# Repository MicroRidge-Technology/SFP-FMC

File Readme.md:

# FMC SFP Card

This project is designed to allow using sfp cables with the LVDS pins of an FPGA as opposed to the GTX pins. It provides testpoints to monitor the lvds signals with an oscilliscope.

# Pins Used

| FMC Pin | Logical Name | SFP Channel |
| ------- | ------------ | ----------- |
| D14     | FMC\_LA09\_P | SFP0 rx+    |
| D15     | FMC\_LA09\_N | SFP0 rx-    |
| H7      | FMC\_LA02\_P | SFP0 tx+    |
| H8      | FMC\_LA02\_N | SFP0 tx-    |
| H22     | FMC\_LA19\_P | SFP1 rx+    |
| H23     | FMC\_LA19\_N | SFP1 rx-    |
| H37     | FMC\_LA32\_P | SFP1 tx+    |
| H38     | FMC\_LA32\_N | SFP1 tx-    |

# Schematics
Schmatics are available [here](doc/fmc-sfp.pdf)

# Images

Top

Bottom

# Limitations 

This board is designed to work with low frequency signals (<200MHz)  GHz+ signals will certainly fail.

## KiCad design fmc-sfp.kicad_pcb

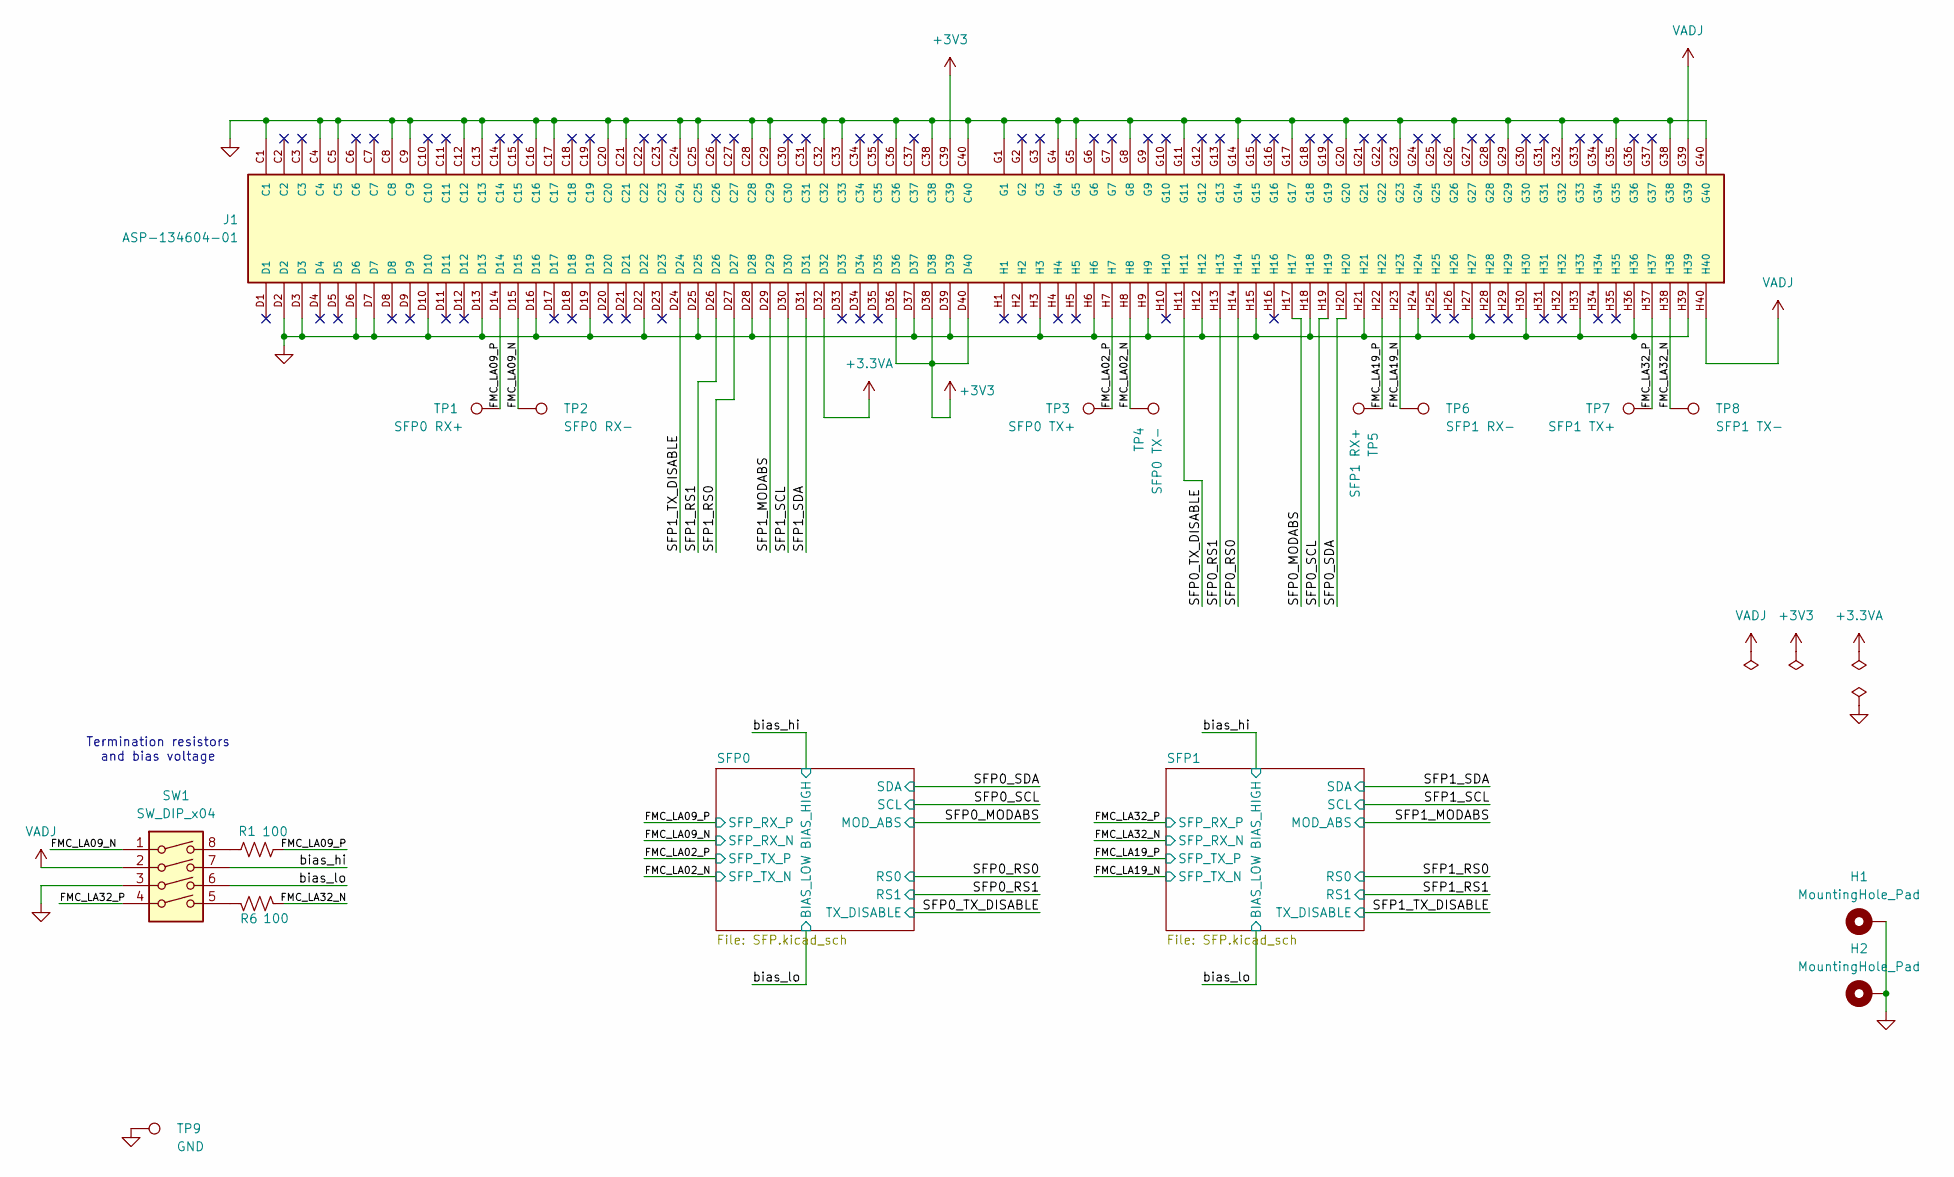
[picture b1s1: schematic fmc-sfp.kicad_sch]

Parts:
H1, H2: MountingHole_Pad; MountingHole_2.7mm_M2.5_ISO14580_Pad
J1: ASP-134604-01; SAMTEC_ASP-134604-01; PARTREV S
R1, R6: 100; R_0805_2012Metric_Pad1.20x1.40mm_HandSolder; MPN 0805W8F1000T5E
SW1: SW_DIP_x04; SW_DIP_SPSTx04_Slide_KingTek_DSHP04TS_W7.62mm_P1.27mm; MPN DSHP04TSGET
TP1: SFP0 RX+; TestPoint_Pad_D2.5mm
TP2: SFP0 RX-; TestPoint_Pad_D2.5mm
TP3: SFP0 TX+; TestPoint_Pad_D2.5mm
TP4: SFP0 TX-; TestPoint_Pad_D2.5mm
TP5: SFP1 RX+; TestPoint_Pad_D2.5mm
TP6: SFP1 RX-; TestPoint_Pad_D2.5mm
TP7: SFP1 TX+; TestPoint_Pad_D2.5mm
TP8: SFP1 TX-; TestPoint_Pad_D2.5mm
TP9: GND; TestPoint_Keystone_5015_Micro-Minature; MPN 5015

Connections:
+3.3VA: J1.D32
+3V3: J1.C39, J1.D36, J1.D38, J1.D40; also elsewhere on the board
/FMC_LA02_N: J1.H8, TP4.1; also elsewhere on the board
/FMC_LA02_P: J1.H7, TP3.1; also elsewhere on the board
/FMC_LA09_N: J1.D15, SW1.1, TP2.1; also elsewhere on the board
/FMC_LA09_P: J1.D14, R1.2, TP1.1; also elsewhere on the board
/FMC_LA19_N: J1.H23, TP6.1; also elsewhere on the board
/FMC_LA19_P: J1.H22, TP5.1; also elsewhere on the board
/FMC_LA32_N: J1.H38, R6.2, TP8.1; also elsewhere on the board
/FMC_LA32_P: J1.H37, SW1.4, TP7.1; also elsewhere on the board
/SFP0_MODABS: J1.H17; also elsewhere on the board
/SFP0_RS0: J1.H14; also elsewhere on the board
/SFP0_RS1: J1.H13; also elsewhere on the board
/SFP0_SCL: J1.H19; also elsewhere on the board
/SFP0_SDA: J1.H20; also elsewhere on the board
/SFP0_TX_DISABLE: J1.H11; also elsewhere on the board
/SFP1_MODABS: J1.D29; also elsewhere on the board
/SFP1_RS0: J1.D27; also elsewhere on the board
/SFP1_RS1: J1.D26; also elsewhere on the board
/SFP1_SCL: J1.D30; also elsewhere on the board
/SFP1_SDA: J1.D31; also elsewhere on the board
/SFP1_TX_DISABLE: J1.D24; also elsewhere on the board
/bias_hi: SW1.7; also elsewhere on the board
/bias_lo: SW1.6; also elsewhere on the board
GND: H1.1, H2.1, J1.C1, J1.C4, J1.C5, J1.C8, J1.C9, J1.C12, J1.C13, J1.C16, J1.C17, J1.C20, J1.C21, J1.C24, J1.C25, J1.C28, J1.C29, J1.C32, J1.C33, J1.C36, J1.C38, J1.C40, J1.D2, J1.D3, J1.D6, J1.D7, J1.D10, J1.D13, J1.D16, J1.D19, J1.D22, J1.D25, J1.D28, J1.D37, J1.D39, J1.G1, J1.G4, J1.G5, J1.G8, J1.G11, J1.G14, J1.G17, J1.G20, J1.G23, J1.G26, J1.G29, J1.G32, J1.G35, J1.G38, J1.G40, J1.H3, J1.H6, J1.H9, J1.H12, J1.H15, J1.H18, J1.H21, J1.H24, J1.H27, J1.H30, J1.H33, J1.H36, J1.H39, SW1.3, TP9.1; also elsewhere on the board
unnamed: R1.1, SW1.8
unnamed: R6.1, SW1.5
VADJ: J1.G39, J1.H40, SW1.2; also elsewhere on the board

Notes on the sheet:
Termination resistors and bias voltage

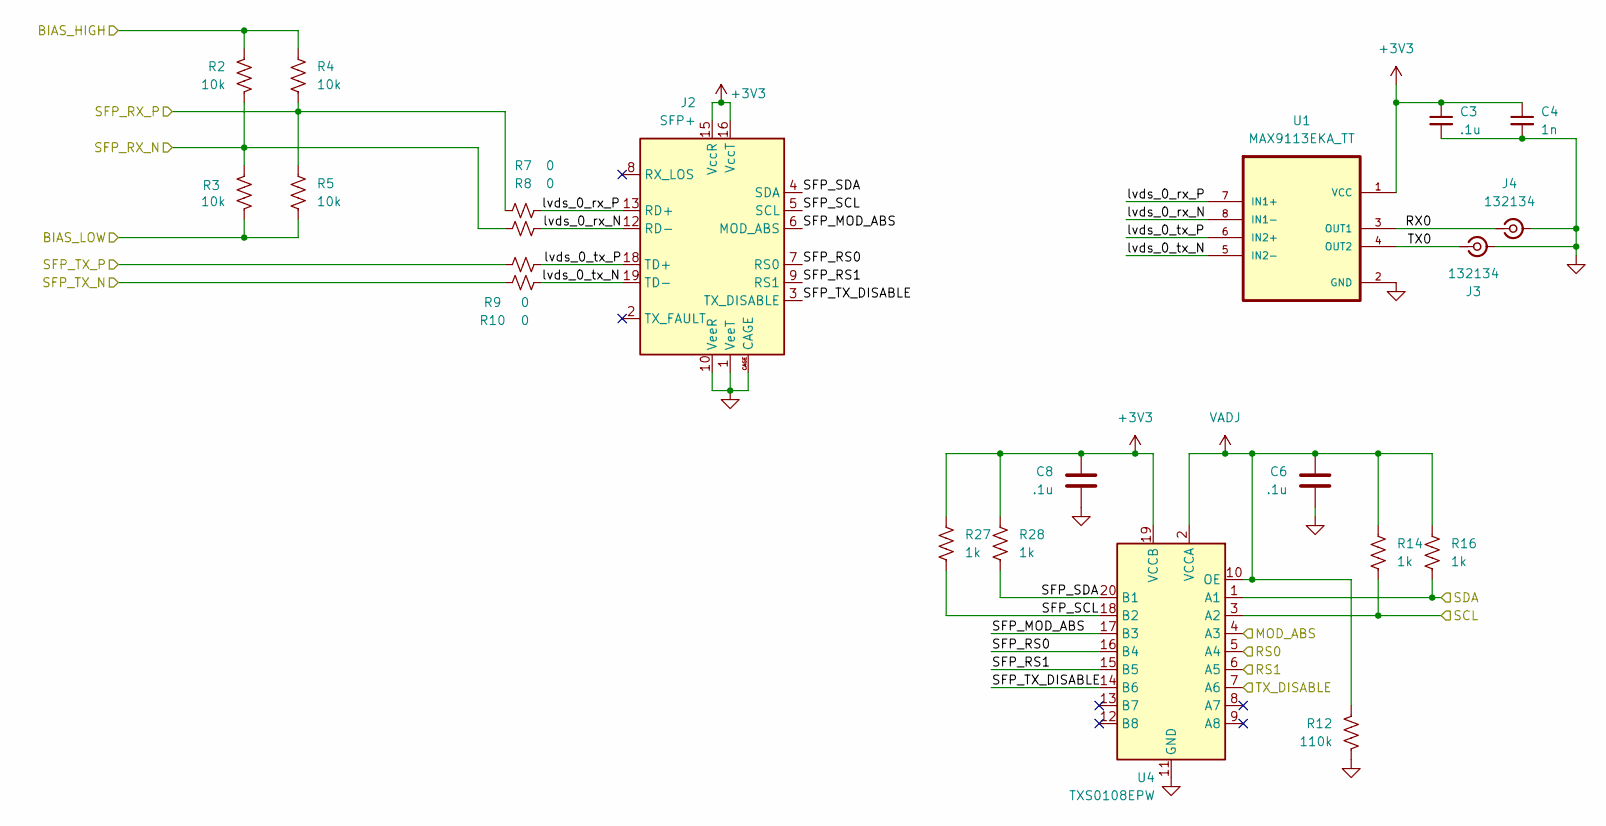
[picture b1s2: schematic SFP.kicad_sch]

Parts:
C3, C6, C8: .1u; C_0603_1608Metric; MPN C0603C104M5RAC7867
C4: 1n; C_0603_1608Metric; MPN C0603C102K5RAC7867
J2: SFP+; SFP_and_Cage; MPN SFPK-SL
J3, J4: 132134; SMA_Amphenol_132134_Vertical; MPN 132134
R2, R3, R4, R5: 10k; R_0805_2012Metric_Pad1.20x1.40mm_HandSolder; MPN 0805W8F1002T5E
R7, R8, R9, R10: 0; R_0805_2012Metric_Pad1.20x1.40mm_HandSolder; MPN 0805W8F0000T5E
R12: 110k; R_0805_2012Metric_Pad1.20x1.40mm_HandSolder; MPN 0805W8F1103T5E
R14, R16, R27, R28: 1k; R_0805_2012Metric_Pad1.20x1.40mm_HandSolder; MPN 0805W8F1001T5E
U1: MAX9113EKA_TT; SOT-23-8; MPN MAX9113EKA+T
U4: TXS0108EPW; TSSOP-20_4.4x6.5mm_P0.65mm; MPN TXS0108EPW

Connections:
+3V3: C3.1, C4.1, C8.1, J2.15 (VccR), J2.16 (VccT), R27.1, R28.1, U1.1 (VCC), U4.19 (VCCB); also elsewhere on the board
/FMC_LA19_N: R10.1; also elsewhere on the board
/FMC_LA19_P: R9.1; also elsewhere on the board
/FMC_LA32_N: R2.2, R3.1, R8.1; also elsewhere on the board
/FMC_LA32_P: R4.2, R5.1, R7.1; also elsewhere on the board
/SFP1/RX0: J4.1 (In), U1.3 (OUT1)
/SFP1/SFP_MOD_ABS: J2.6 (MOD_ABS), U4.17 (B3)
/SFP1/SFP_RS0: J2.7 (RS0), U4.16 (B4)
/SFP1/SFP_RS1: J2.9 (RS1), U4.15 (B5)
/SFP1/SFP_SCL: J2.5 (SCL), R27.2, U4.18 (B2)
/SFP1/SFP_SDA: J2.4 (SDA), R28.2, U4.20 (B1)
/SFP1/SFP_TX_DISABLE: J2.3 (TX_DISABLE), U4.14 (B6)
/SFP1/TX0: J3.1 (In), U1.4 (OUT2)
/SFP1/lvds_0_rx_N: J2.12 (RD-), R8.2, U1.8 (IN1-)
/SFP1/lvds_0_rx_P: J2.13 (RD+), R7.2, U1.7 (IN1+)
/SFP1/lvds_0_tx_N: J2.19 (TD-), R10.2, U1.5 (IN2-)
/SFP1/lvds_0_tx_P: J2.18 (TD+), R9.2, U1.6 (IN2+)
/SFP1_MODABS: U4.4 (A3); also elsewhere on the board
/SFP1_RS0: U4.5 (A4); also elsewhere on the board
/SFP1_RS1: U4.6 (A5); also elsewhere on the board
/SFP1_SCL: R14.2, U4.3 (A2); also elsewhere on the board
/SFP1_SDA: R16.2, U4.1 (A1); also elsewhere on the board
/SFP1_TX_DISABLE: U4.7 (A6); also elsewhere on the board
/bias_hi: R2.1, R4.1; also elsewhere on the board
/bias_lo: R3.2, R5.2; also elsewhere on the board
GND: C3.2, C4.2, C6.2, C8.2, J2.1 (VeeT), J2.10 (VeeR), J2.11 (VeeR), J2.14 (VeeR), J2.17 (VeeT), J2.20 (VeeT), J2.CAGE, J3.2 (Ext), J4.2 (Ext), R12.2, U1.2 (GND), U4.11 (GND); also elsewhere on the board
VADJ: C6.1, R12.1, R14.1, R16.1, U4.2 (VCCA), U4.10 (OE); also elsewhere on the board

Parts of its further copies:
C1, C5, C7: .1u; C_0603_1608Metric; MPN C0603C104M5RAC7867
C2: 1n; C_0603_1608Metric; MPN C0603C102K5RAC7867
J8: SFP+; SFP_and_Cage; MPN SFPK-SL
J9, J10: 132134; SMA_Amphenol_132134_Vertical; MPN 132134
R11: 110k; R_0805_2012Metric_Pad1.20x1.40mm_HandSolder; MPN 0805W8F1103T5E
R13, R15, R17, R18: 1k; R_0805_2012Metric_Pad1.20x1.40mm_HandSolder; MPN 0805W8F1001T5E
R19, R20, R21, R22: 10k; R_0805_2012Metric_Pad1.20x1.40mm_HandSolder; MPN 0805W8F1002T5E
R23, R24, R25, R26: 0; R_0805_2012Metric_Pad1.20x1.40mm_HandSolder; MPN 0805W8F0000T5E
U2: TXS0108EPW; TSSOP-20_4.4x6.5mm_P0.65mm; MPN TXS0108EPW
U3: MAX9113EKA_TT; SOT-23-8; MPN MAX9113EKA+T

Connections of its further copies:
+3V3: C1.1, C2.1, C7.1, J8.15 (VccR), J8.16 (VccT), R17.1, R18.1, U2.19 (VCCB), U3.1 (VCC); also elsewhere on the board
/FMC_LA02_N: R26.1; also elsewhere on the board
/FMC_LA02_P: R25.1; also elsewhere on the board
/FMC_LA09_N: R19.2, R20.1, R24.1; also elsewhere on the board
/FMC_LA09_P: R21.2, R22.1, R23.1; also elsewhere on the board
/SFP0/RX0: J10.1 (In), U3.3 (OUT1)
/SFP0/SFP_MOD_ABS: J8.6 (MOD_ABS), U2.17 (B3)
/SFP0/SFP_RS0: J8.7 (RS0), U2.16 (B4)
/SFP0/SFP_RS1: J8.9 (RS1), U2.15 (B5)
/SFP0/SFP_SCL: J8.5 (SCL), R17.2, U2.18 (B2)
/SFP0/SFP_SDA: J8.4 (SDA), R18.2, U2.20 (B1)
/SFP0/SFP_TX_DISABLE: J8.3 (TX_DISABLE), U2.14 (B6)
/SFP0/TX0: J9.1 (In), U3.4 (OUT2)
/SFP0/lvds_0_rx_N: J8.12 (RD-), R24.2, U3.8 (IN1-)
/SFP0/lvds_0_rx_P: J8.13 (RD+), R23.2, U3.7 (IN1+)
/SFP0/lvds_0_tx_N: J8.19 (TD-), R26.2, U3.5 (IN2-)
/SFP0/lvds_0_tx_P: J8.18 (TD+), R25.2, U3.6 (IN2+)
/SFP0_MODABS: U2.4 (A3); also elsewhere on the board
/SFP0_RS0: U2.5 (A4); also elsewhere on the board
/SFP0_RS1: U2.6 (A5); also elsewhere on the board
/SFP0_SCL: R13.2, U2.3 (A2); also elsewhere on the board
/SFP0_SDA: R15.2, U2.1 (A1); also elsewhere on the board
/SFP0_TX_DISABLE: U2.7 (A6); also elsewhere on the board
/bias_hi: R19.1, R21.1; also elsewhere on the board
/bias_lo: R20.2, R22.2; also elsewhere on the board
GND: C1.2, C2.2, C5.2, C7.2, J8.1 (VeeT), J8.10 (VeeR), J8.11 (VeeR), J8.14 (VeeR), J8.17 (VeeT), J8.20 (VeeT), J8.CAGE, J9.2 (Ext), J10.2 (Ext), R11.2, U2.11 (GND), U3.2 (GND); also elsewhere on the board
VADJ: C5.1, R11.1, R13.1, R15.1, U2.2 (VCCA), U2.10 (OE); also elsewhere on the board

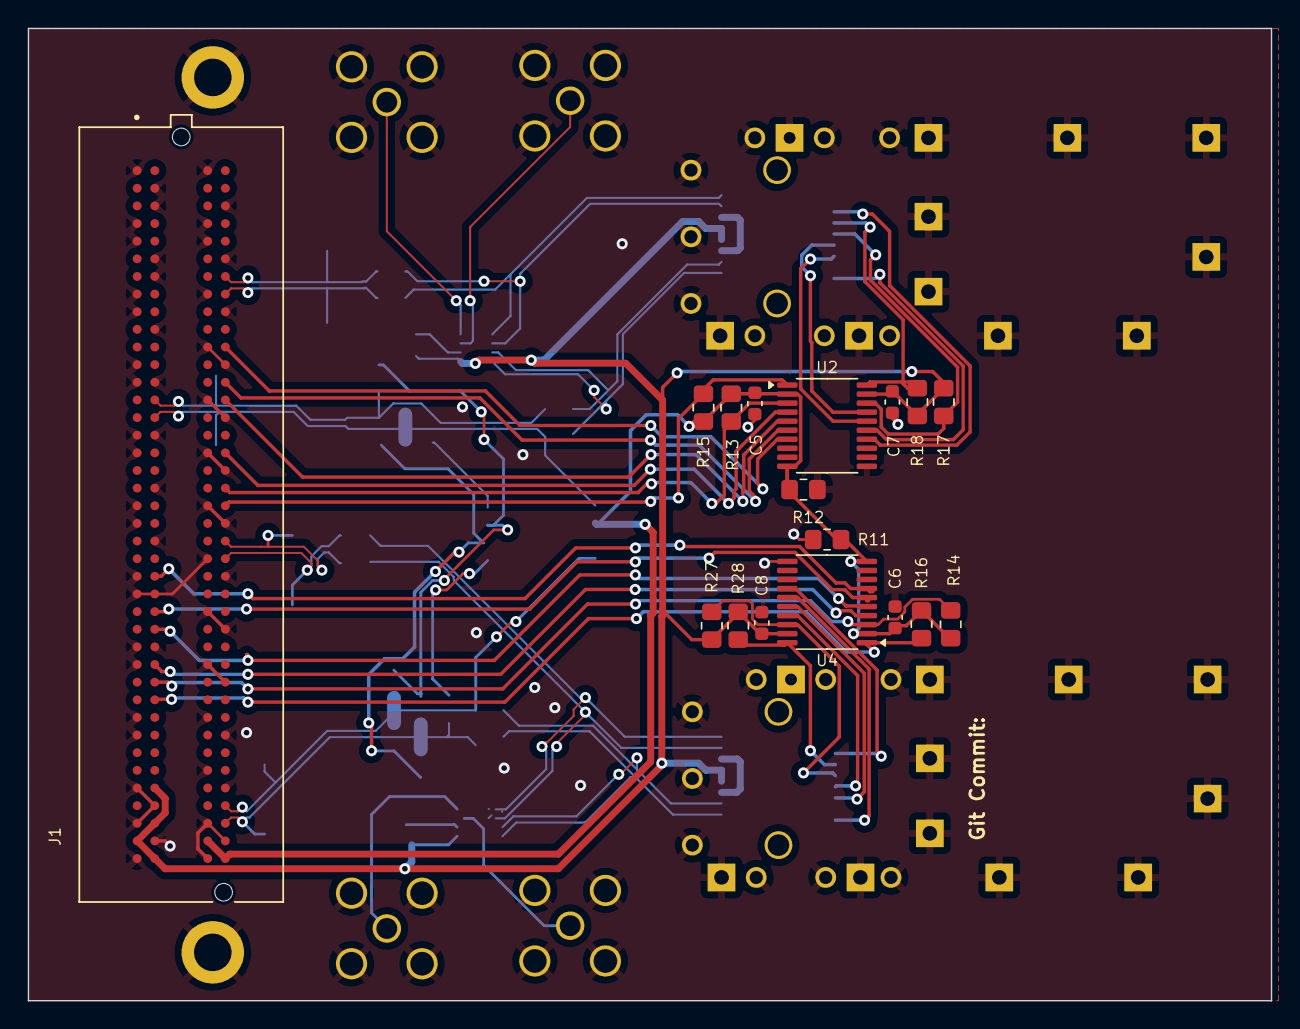
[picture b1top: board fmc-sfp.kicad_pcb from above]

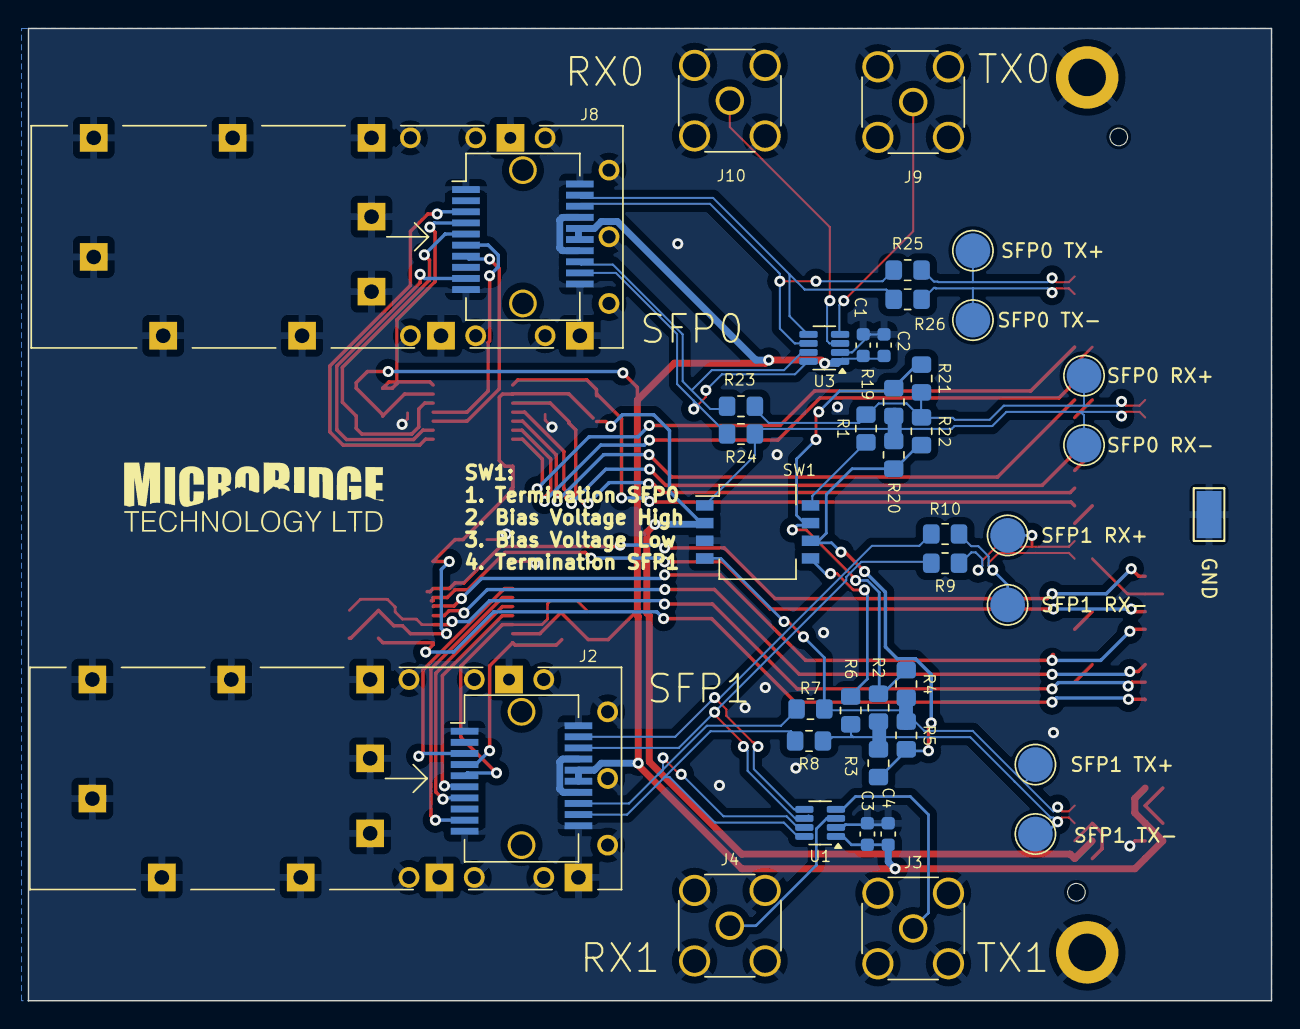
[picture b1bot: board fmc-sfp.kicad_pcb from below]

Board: 4 copper layers, 89.5 x 70.0 mm, 59 parts (40 on the bottom side), 51 nets.

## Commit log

2024-05-03 change fmc connector model
2024-05-03 add some docs
2024-05-03 add 3d models
2024-05-03 change schematic directory
2024-05-03 update bottom image
2024-05-03 update schematic
2024-05-03 update after Phil review
2024-05-03 add sfp module step model
2024-05-03 Minor tweaks to sfp cage position, fix silkscreen s/RX/TX/
2024-05-03 update 3d images
2024-05-04 move termination resistors to FPGA side of capacitors
2024-05-04 clean up a trace
2024-05-08 update capacitor part numbers
2024-05-08 connect all grounds for fmc connector
2024-05-08 add fmc footprint to project
2024-05-08 Change part numbers for nextpcb
2024-05-09 change 0402 Resister for 0603 resistor
2024-05-14 create gh action
2024-05-14 actions run as root
2024-05-14 fix typo
2024-05-14 update sfp footprint, add git commit to silkscreen
2024-05-14 try safe.directory
2024-05-14 rename artifacts
2024-05-14 set part number for sfp cage
2024-05-30 modify title block
2024-05-30 update schematic pdf
2024-05-30 Change resistors to 0805, add switch to disable DC Bias
2024-05-30 add schematic to generated files
2024-05-30 run action on tags as well
2024-05-30 actions do deep checkout
2024-05-30 use custom schematic page layout
2024-05-31 remove unused file
2024-05-31 fix ERC
2024-05-31 run DRC and generate board files
2024-05-31 fix Vadj symbol
2024-05-31 fix github workflow
2024-05-31 clean up schematic and pcb
2024-05-31 make board more symetrical
2024-05-31 board_files.sh automatically calls docker if necessary
2024-06-11 add single x4 switch and test pads for differential probing
2024-06-11 fix DRC issues
2024-06-11 cleanup schematic
2024-06-11 update documents
2024-06-11 exclude test points from BOM
2024-06-11 asthetic cleanup, add ground testpoint
2024-06-14 set SW1 part number
2024-06-14 change version string
2024-06-14 move GND TP lable
2024-06-14 update schematics with I2C
2024-06-15 Update layout with i2c
2024-06-15 add level shifter Part Number
2024-06-17 update fills
2024-06-17 Update MPN of switch
2024-07-06 fix MPN of 110K resistors
2024-07-26 Update PDF of schematics in doc directory
2024-08-06 Add Title block to other sheets
2024-08-06 update title block
2025-07-24 Update Readme.md with limitations
